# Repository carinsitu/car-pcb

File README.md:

# CarInSitu PCB for RC car

This repository contains _KiCAD_ files related to RC car's PCB.

Its licensed under _GPLv3_.

↑ The above photo is of proto 1

## Features

 - ESP82xx MCU
 - External antenna through UFL connector (using Lolin D1 mini pro)
 - Front head light (High-efficiency LEDs)
 - RBG LED port (APA106/WS2812)
 - PPM-driven ESC for brushed motor (external module based)
 - PPM-driven steering
 - IR receiver
 - VTX port (UART)
 - IMU
 - Battery gauge

↑ The above screenshot is a 3D preview of v0.4

## Manufacturing note

The PCB is designed with "standard" isolation (≥ 6 mil) for the most part, except in the area of the IMU (U7) whose package is just under 6 mil.

There are overlapping components:
- R1, C12, C13 with U1: U1 is high enough for this to work
- RB5 with RB10: one pad is common so that they are not on board together

## Misc

Note: Feel free to contact [neomilium](https://github.com/neomilium) if you want to turn this into commercial product.

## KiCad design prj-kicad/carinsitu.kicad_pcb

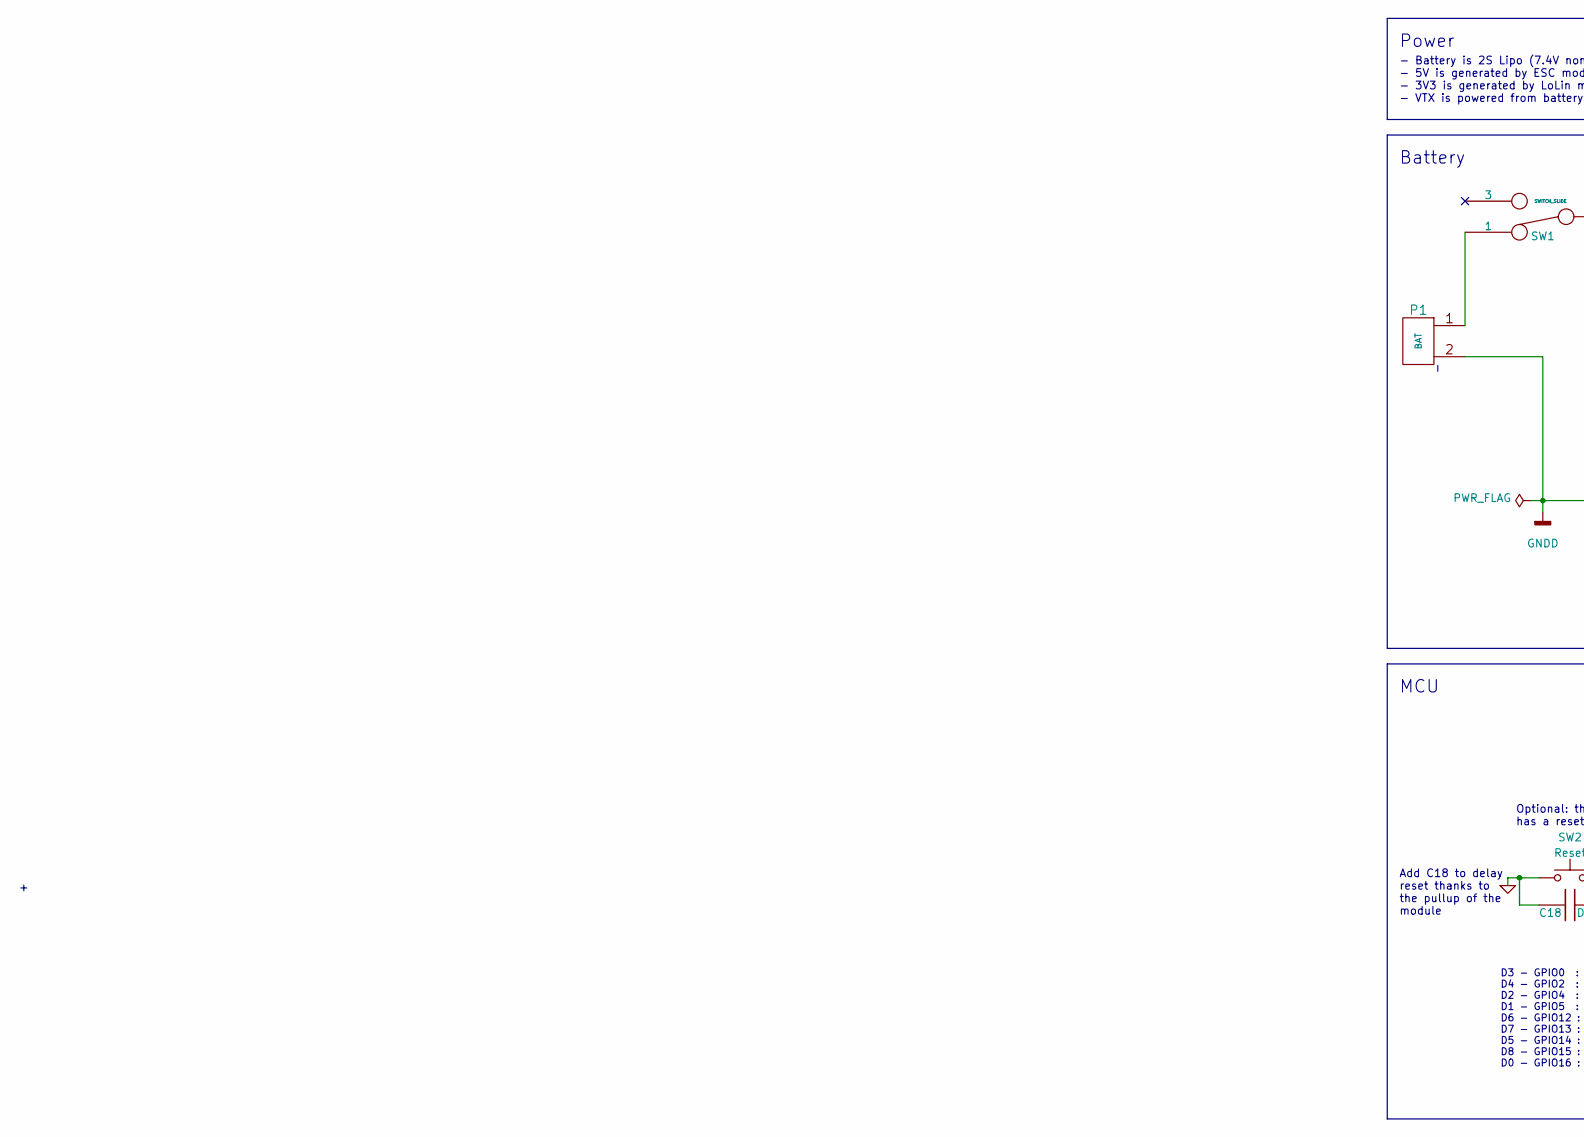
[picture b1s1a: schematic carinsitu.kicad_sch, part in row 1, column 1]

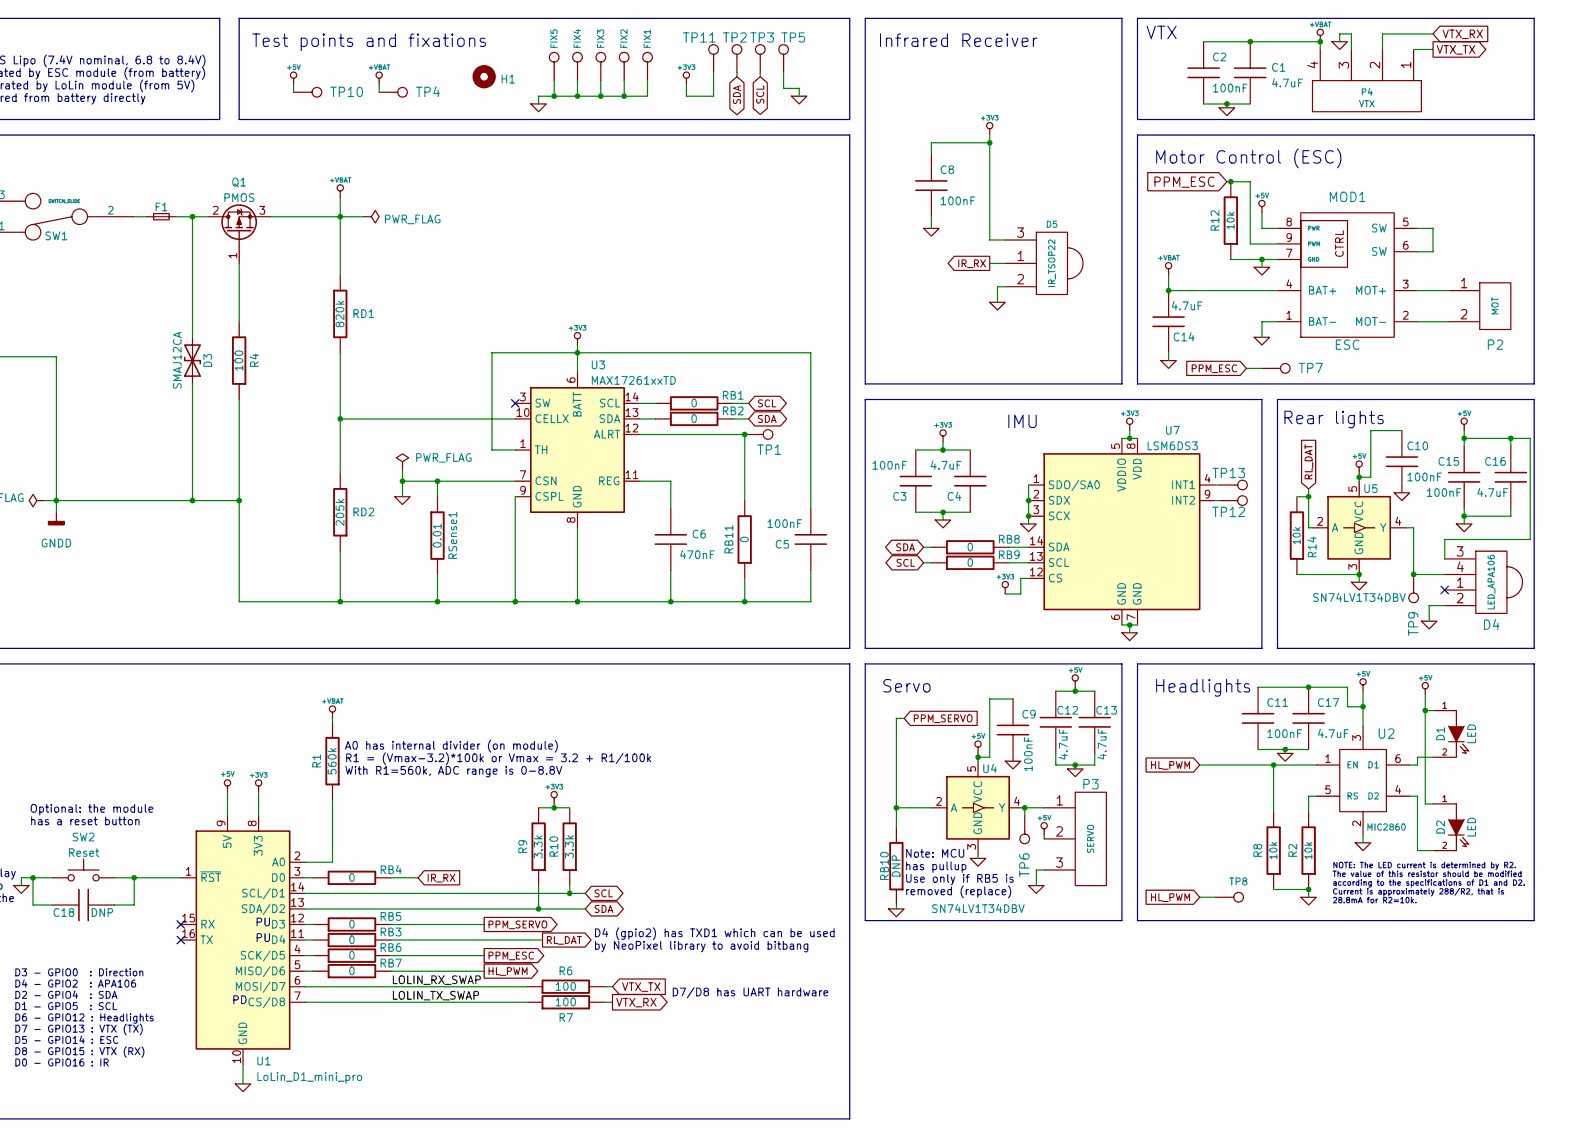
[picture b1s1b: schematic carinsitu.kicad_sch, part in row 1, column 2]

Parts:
C1, C4, C12, C13, C14, C16, C17: 4.7uF; C_0805_2012Metric
C2, C3, C5, C8, C9, C10, C11, C15: 100nF; C_0603_1608Metric
C6: 470nF; C_0603_1608Metric
C18: DNP; C_0805_2012Metric
D1, D2: LED; LED_D5.0mm_Horizontal_O3.81mm_Z3.0mm
D3: SMAJ12CA; D_SMA
D4: LED_APA106; LED-APA106
D5: IR_TSOP22; CONN_61300311121
F1: Fuse; Fuse_Littelfuse_395Series
FIX1, FIX2, FIX3, FIX4, FIX5: CONN_1; FIX
H1: MountingHole; VTX_avatar_halfholes
MOD1: ESC
P1: BAT; CONN_61300211021
P2: MOT; CONN_JST-XH-2
P3: SERVO; CONN_61300311021
P4: VTX; CONN_61300411121
Q1: PMOS; TO-252-2
R1: 560k; R_0805_2012Metric
R2, R8, R12, R14: 10k; R_0805_2012Metric
R4, R6, R7: 100; R_0805_2012Metric
R9, R10: 3.3k; R_0805_2012Metric
RB1, RB2, RB3, RB4, RB5, RB6, RB7, RB8, RB9, RB11: 0; R_0603_1608Metric
RB10: DNP; R_0603_1608Metric
RD1: 820k; R_0805_2012Metric
RD2: 205k; R_0805_2012Metric
RSense1: 0.01; R_2010_5025Metric
SW1: SWITCH_SLIDE; SW_L102xxxML
SW2: Reset; SW_Push_SPST_NO_Alps_SKRK
TP1, TP2, TP3, TP4, TP5, TP6, TP7, TP8, TP9, TP10, TP11, TP12, TP13: CONN_1; TP
U1: LoLin_D1_mini_pro; WEMOS_D1_mini_light
U2: MIC2860; SOT-23-6
U3: MAX17261xxTD; TDFN-14-1EP_3x3mm_P0.4mm_EP1.78x2.35mm
U4, U5: SN74LV1T34DBV; SOT-23-5
U7: LSM6DS3; LGA-14_3x2.5mm_P0.5mm_LayoutBorder3x4y

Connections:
+3V3: C3.2, C4.2, C5.2, C8.1, D5.3 (VDD), R9.2, R10.2, TP11.1, U1.8 (3V3), U3.1 (TH), U3.6 (BATT), U7.5 (VDDIO), U7.8 (VDD), U7.12 (CS)
+5V: C9.1, C10.1, C11.1, C12.1, C13.1, C15.1, C16.1, C17.1, D1.1 (A), D2.1 (A), D4.3 (VDD), MOD1.8 (PWR), P3.2, TP10.1, U1.9 (5V), U2.3, U4.5 (VCC), U5.5 (VCC)
+VBAT: C1.1, C2.1, C14.2, MOD1.4 (BAT+), P4.4, Q1.3 (S), R1.2, RD1.1, TP4.1
/LOLIN_RX_SWAP: R6.1, U1.6 (MOSI/D7)
/LOLIN_TX_SWAP: R7.1, U1.7 (CS/D8)
GND: C1.2, C2.2, C3.1, C4.1, C8.2, C9.2, C10.2, C11.2, C12.2, C13.2, C14.1, C15.2, C16.2, C17.2, C18.1, D4.2 (GND), D5.2 (GND), FIX1.1, FIX2.1, FIX3.1, FIX4.1, FIX5.1, MOD1.1 (BAT-), MOD1.7 (GND), P3.3, P4.3, R2.1, R8.1, R12.1, R14.1, RB10.1, RSense1.1, SW2.1, TP5.1, U1.10 (GND), U2.2, U3.7 (CSN), U4.3 (GND), U5.3 (GND), U7.1 (SDO/SA0), U7.2 (SDX), U7.3 (SCX), U7.6 (GND), U7.7 (GND)
GNDD: C5.1, C6.2, D3.1 (A1), P1.2 (PM), R4.1, RB11.1, RD2.1, RSense1.2, U3.8 (GND), U3.9 (CSPL), U3.15 (GND)
HL_PWM: R8.2, RB7.2, TP8.1, U2.1 (EN)
IR_RX: D5.1 (DOUT), RB4.2
unnamed: C6.1, U3.11 (REG)
unnamed: C18.2, SW2.2, U1.1 (~RST)
unnamed: D1.2 (K), U2.6 (D1)
unnamed: D2.2 (K), U2.4 (D2)
unnamed: D3.2 (A2), F1.2, Q1.2 (D)
unnamed: D4.4 (DIN), TP9.1, U5.4 (Y)
unnamed: F1.1, SW1.2
unnamed: MOD1.2 (MOT-), P2.2 (PM)
unnamed: MOD1.3 (MOT+), P2.1
unnamed: MOD1.5 (SW), MOD1.6 (SW)
unnamed: P1.1, SW1.1
unnamed: P3.1, TP6.1, U4.4 (Y)
unnamed: Q1.1 (G), R4.2
unnamed: R1.1, U1.2 (A0)
unnamed: R2.2, U2.5 (RS)
unnamed: RB1.1, U3.14 (SCL)
unnamed: RB2.1, U3.13 (SDA)
unnamed: RB3.1, U1.11 (D4)
unnamed: RB4.1, U1.3 (D0)
unnamed: RB5.1, U1.12 (D3)
unnamed: RB6.1, U1.4 (SCK/D5)
unnamed: RB7.1, U1.5 (MISO/D6)
unnamed: RB8.2, U7.14 (SDA)
unnamed: RB9.2, U7.13 (SCL)
unnamed: RB11.2, TP1.1, U3.12 (ALRT)
unnamed: RD1.2, RD2.2, U3.10 (CELLX)
unnamed: TP12.1, U7.9 (INT2)
unnamed: TP13.1, U7.4 (INT1)
PPM_ESC: MOD1.9 (PWM), R12.2, RB6.2, TP7.1
PPM_SERVO: RB5.2, RB10.2, U4.2 (A)
RL_DAT: R14.2, RB3.2, U5.2 (A)
SCL: R10.1, RB1.2, RB9.1, TP3.1, U1.14 (SCL/D1)
SDA: R9.1, RB2.2, RB8.1, TP2.1, U1.13 (SDA/D2)
VTX_RX: P4.2, R7.2
VTX_TX: P4.1, R6.2

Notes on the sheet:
Optional: the module has a reset button
D7/D8 has UART hardware
MCU
A0 has internal divider (on module) R1 = (Vmax-3.2)*100k or Vmax = 3.2 + R1/100k With R1=560k, ADC range is 0-8.8V
Test points and fixations
NOTE: The LED current is determined by R2. The value of this resistor should be modified according to the specifications of D1 and D2. Current is approximately 288/R2, that is 28.8mA for R2=10k.
Motor Control (ESC)
D3 - GPIO0 : Direction D4 - GPIO2 : APA106 D2 - GPIO4 : SDA D1 - GPIO5 : SCL D6 - GPIO12 : Headlights D7 - GPIO13 : VTX (TX) D5 - GPIO14 : ESC D8 - GPIO15 : VTX (RX) D0 - GPIO16 : IR
Battery
Note: MCU has pullup Use only if RB5 is removed (replace)
Add C18 to delay reset thanks to the pullup of the module
Rear lights
VTX
D4 (gpio2) has TXD1 which can be used by NeoPixel library to avoid bitbang
Infrared Receiver
IMU
Headlights
Power
- Battery is 2S Lipo (7.4V nominal, 6.8 to 8.4V) - 5V is generated by ESC module (from battery) - 3V3 is generated by LoLin module (from 5V) - VTX is powered from battery directly
Servo

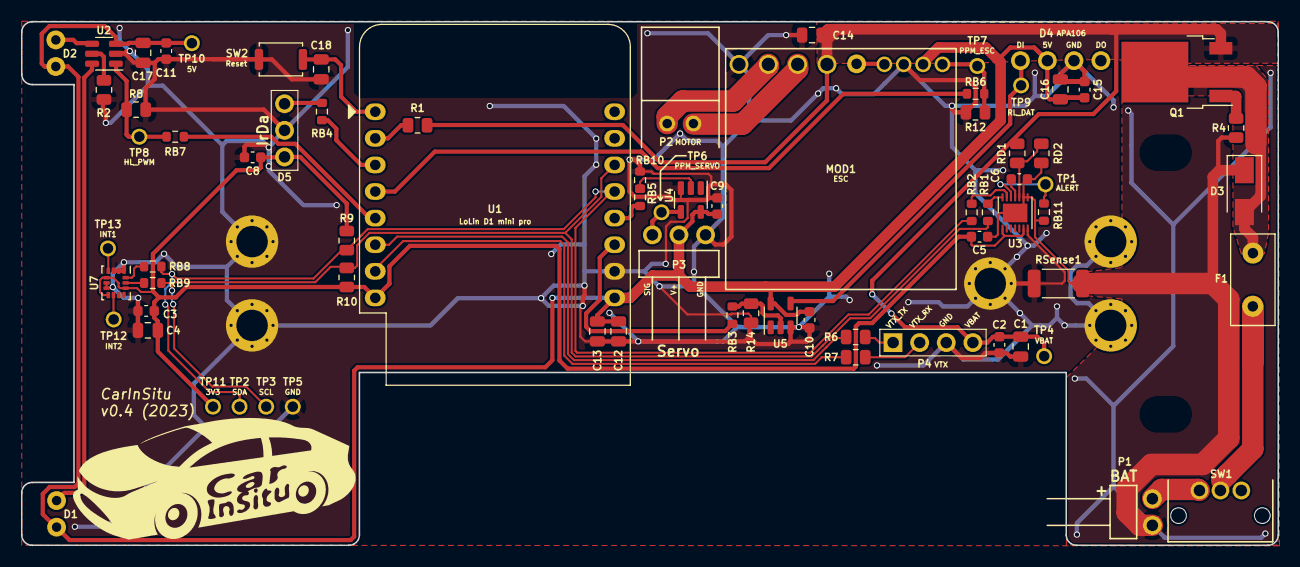
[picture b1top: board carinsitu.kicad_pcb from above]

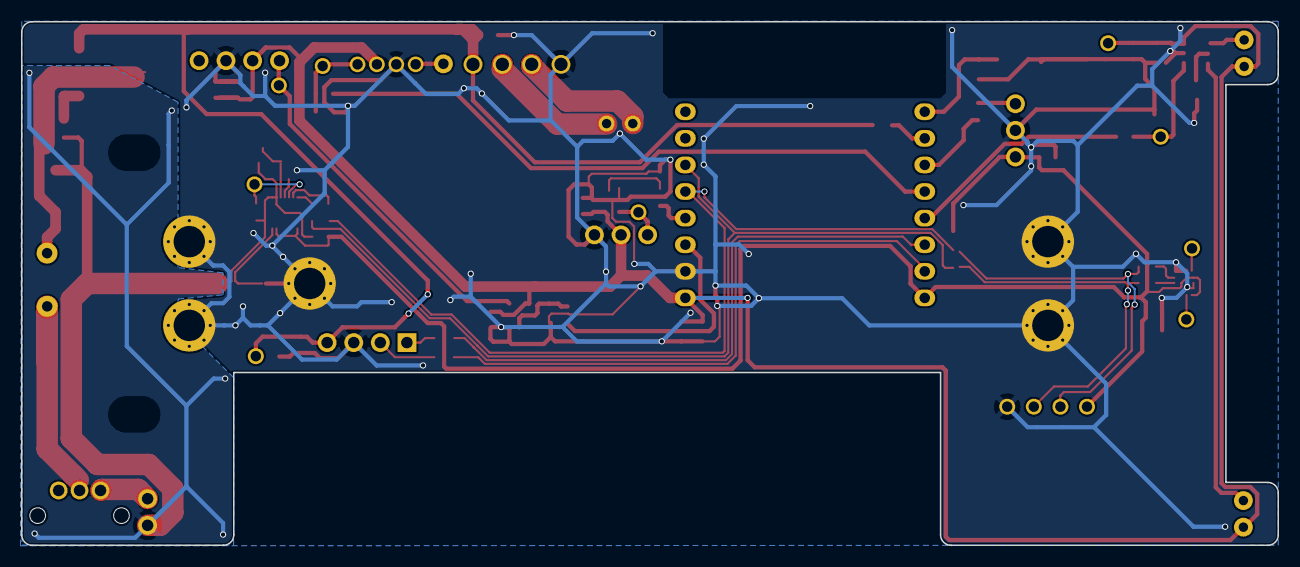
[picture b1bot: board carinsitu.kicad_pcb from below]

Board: 2 copper layers, 120.0 x 50.0 mm, 80 parts (2 on the bottom side), 44 nets.

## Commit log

2019-06-18 --=={ Create Project }==--
2019-06-18 = ADD: Draw board outline, add fix holes
2019-06-26 = ADD: Place headlight LEDs, motor connector and ESC outline
2019-07-01 = ADD: Create ESP32 interface ; create schematics and footprint for Wemos D1-Mini (not fully routed)
2019-07-03 = ADD: Insert a slide switch to connect power (on / off)
2019-07-03 = ADD: Insert battery monitor (STC3100)
2019-07-03 = ADD: insert a 3 pin connector for servo (direction)
2019-07-03 = ADD: insert second RGB led and add a level switch (3V3 -> 5V) on data line
2019-07-03 = CLEAN: Re-order schematic blocks and add comments
2019-07-03 = ADD: insert a 3V3 power regulator. Schematic and place ok, routing not complete
2019-07-03 = ADD: insert iNEMO inertial chip (LSM6DS3) - Routing not complete
2019-07-05 = UPD: Improve RGB LED position (according to CAD specs) and power routing
2019-07-05 = UPD: Replace ESP32 with ESP82xx to fit software requirements
2019-07-08 = UPD: Improve ESP82xx routing, connect main IOs (leds, esc, servo, ...)
2019-07-09 = UPD: Move power button and servo connector
2019-07-10 = UPD: Replace battery gauge (STC3100 limited to 1 cell) by a MAX17205 ic
2019-07-10 = UPD: re-generate the board 3D preview
2019-07-10 = ADD: Insert test points for I2C and battery (2.54 grid)
2019-07-15 = UPD: Improve power (add decoupling caps), Add test-points for main signals, Add a level shifter for servo
2019-07-16 = UPD: Improve power, fix 3V3 reg footprint and add routing
2019-07-16 = UPD: Improve U3 routing (bat gauge) reduce soldermask and solderpaste for a better isolation
2019-07-17 = ADD: Generate production files for PCB (Gerber + drill)
2019-07-17 = UPD: Add extra-informations on schematics for BOM
2019-07-20 = ADD: Pictures of the first prototype
2019-07-21 = ADD: Write a basic firmware to test ESP chip (and LEDs)
2019-08-06 = NOT: Create a todo-list for the next revision
2019-08-09 = UPD: Rotate headlights LEDs
2019-08-09 = UPD: Move headlights driver and add a logic ic to invert signal
2019-08-09 = DOC: Update 3D preview of rev 2
2023-01-05 README: Introduce project, add license, fix typos
2023-01-05 README: Move and rework ToDo list into dedicated file
2023-01-05 README: List features
2023-01-05 Move a lot of components on the PCB to the right
2023-01-05 PCB: move IrDa
2023-01-07 Update KiCAD project to recent version (6.0)
2023-01-07 Fix schematic DRC
2023-01-07 Sync PCB with schematic
2023-01-07 Do TODO for rear lights
2023-01-07 Exlude PCB DRC warnings for silkscreen
2023-01-07 Move components listed in TODO
2023-01-07 Do the remaining TODO list
2023-01-07 Add logo on PCB
2023-01-07 PCB: Various adjustments
2023-01-09 Reduce length of the board
2023-01-09 Update prod/ files
2023-01-17 reboot du pcb
2023-01-18 cad from old project
2023-01-21 Change MCU and VTX + related (see detailed message)
    The VTX module is changed and now communicates with an UART.
    The MCU and its powering are replaced by a LoLin D1 mini pro module.
    IO are remapped
    Removed inverter on headlights (not needed with new mapping)
    Added pull-up on I²C and pull-down on ESC and Headlights
2023-01-21 Add precisions in note for headlights
2023-01-21 Add spacer in PCB comment layer to have its shape displayed
2023-01-24 Add zero ohm resistors
2023-01-24 Redesign IMU connections
2023-01-25 review Max17215 Fuel Gauge Add missing cap values
2023-01-26 review MAX17205 Fuel Gauge Add missing cap values
2023-01-27 Update PCB + schematic adjustments
    Notable schematic changes:
    - change level shifters for SN74LV1T34DBV (simplify routing)
    - add fuse inversion protection
2023-01-30 Change battery monitor MAX17044G in schematic
2023-01-30 Route new battery monitor
2023-01-31 Reduce board size
2023-01-31 Move components that were under the ESC outside
2023-02-01 Move D3
2023-02-01 Move P3 (servo connector)
2023-02-01 Move IrDa connector and reset button under the windscreen of the car
2023-02-01 Move U5 and other mods
2023-02-03 Change some footprints for kicad lib ones + silkscreen + route adjustments
2023-02-03 Add decoupling capacitors + RB10
2023-02-03 Move U3 and its companions
2023-02-03 Add VTX holes (WIP, bottom right needs rerouting)
2023-02-05 Change input protection and its routing
2023-02-05 Adjust small things on PCB
2023-02-06 Move VTX holes slightly + adjust around BAT connector
2023-02-06 Move Servo connector out of spacer + invert Motor connector to gain place
2023-02-07 Add other decoupling capacitors and route them
2023-02-07 Fix GND pin type of ESC
2023-02-07 Add TVS diode protection
2023-02-07 Reroute 5V to clear U1 module antenna zone
2023-02-07 Round pointy corners
2023-02-07 Add reset capacitor
2023-02-07 Do minor adjustments on PCB
2023-02-07 Add manufacturing note in README
2023-02-08 use max17261 as battry gauge
2023-02-09 schematic corrections and first PCB update
2023-02-09 pcb update -wip-
2023-02-09 Max17261 circuit added
2023-02-12 Change schematic to have everything on one page
2023-02-12 Improve routing of battery gauge
2023-02-12 Remove thermal pad around fixation holes
2023-02-12 Populate most info for BOM, and update PCB
2023-02-12 Change fuse value and PCB layout
2023-02-12 Update manufacturing note in README with new components
2023-02-13 Add test point on battery alert signal
2023-02-13 Update gerbers
2023-02-13 Update README and PCB preview
2023-02-13 Fix net names and isolation rule for IMU on PCB
2023-02-13 Fix Fab layer readability
2023-02-13 Add PDF export
2023-02-14 update BOM
2023-02-14 Add reference for headlight
2023-02-15 Fix a manufacturer's name in bom
2023-02-15 Update properties from schematic on PCB
2023-02-15 Add HTML interactiv BOM
2023-02-15 Update PDF export
2024-04-30 README: Update comments
